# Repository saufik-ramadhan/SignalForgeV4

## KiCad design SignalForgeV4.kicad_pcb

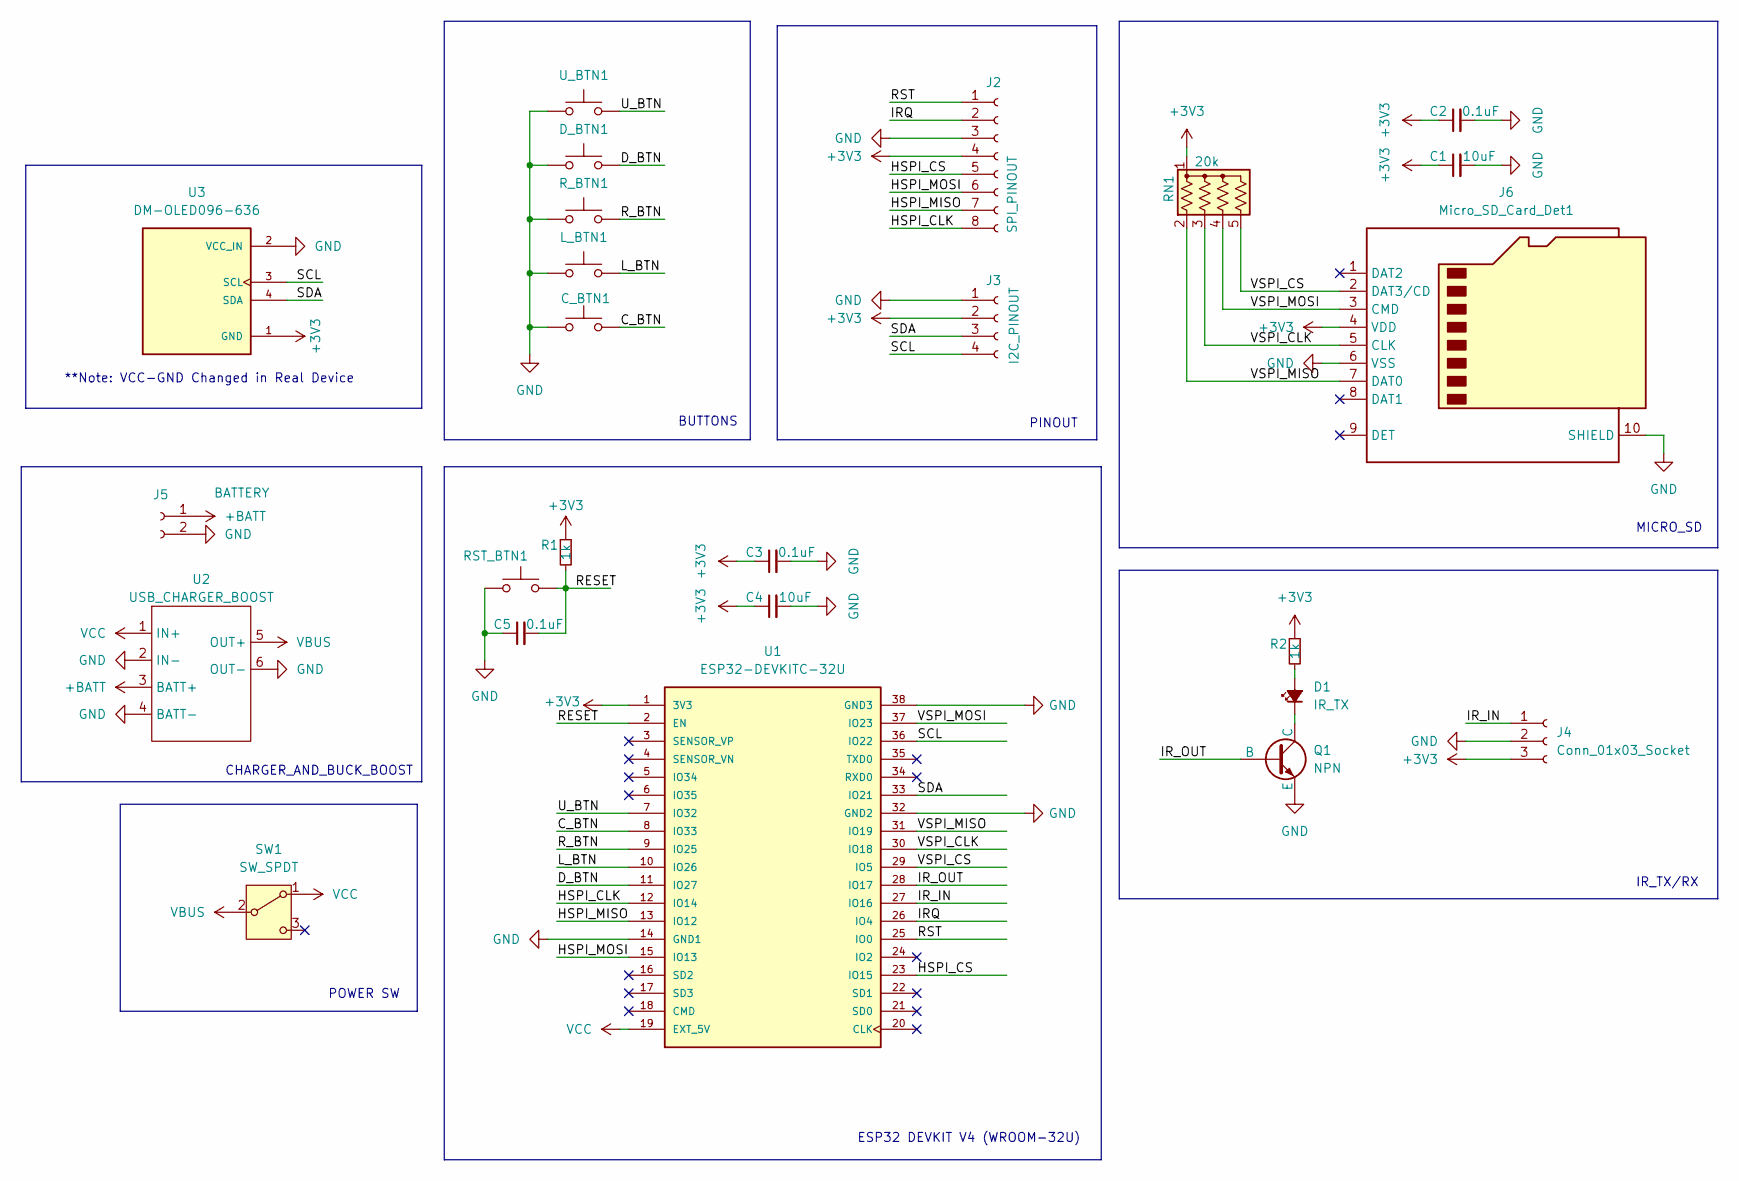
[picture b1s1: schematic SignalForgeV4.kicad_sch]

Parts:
C1, C4: 10uF; C_0805_2012Metric_Pad1.18x1.45mm_HandSolder
C2, C3, C5: 0.1uF; C_0805_2012Metric_Pad1.18x1.45mm_HandSolder
C_BTN1: SW_Push; SW_PUSH_1P1T_6x3.5mm_H5.0_APEM_MJTP1250
D1: IR_TX; PinSocket_1x02_P2.54mm_Vertical
D_BTN1: SW_Push; SW_PUSH_1P1T_6x3.5mm_H5.0_APEM_MJTP1250
J2: SPI_PINOUT; PinSocket_1x08_P2.54mm_Vertical
J3: I2C_PINOUT; PinSocket_1x04_P2.54mm_Vertical
J4: Conn_01x03_Socket; PinSocket_1x03_P2.54mm_Vertical
J5: BATTERY; JST_EH_S2B-EH_1x02_P2.50mm_Horizontal
J6: Micro_SD_Card_Det1; J_SD_Card-micro_socket_A
L_BTN1: SW_Push; SW_PUSH_1P1T_6x3.5mm_H5.0_APEM_MJTP1250
Q1: NPN; SOT-23_Handsoldering
R1, R2: 1k; R_0805_2012Metric_Pad1.20x1.40mm_HandSolder
RN1: 20k; R_Array_Convex_4x0603
RST_BTN1: SW_Push; SW_SPST_FSMSM
R_BTN1: SW_Push; SW_PUSH_1P1T_6x3.5mm_H5.0_APEM_MJTP1250
SW1: SW_SPDT; SW_SPDT_PCM12
U1: ESP32-DEVKITC-32U; MODULE_ESP32-DEVKITC-32U; PARTREV V4
U2: USB_CHARGER_BOOST; USB_Charger_Buck_Boost
U3: DM-OLED096-636; MODULE_DM-OLED096-636; PARTREV 2018-09-10
U_BTN1: SW_Push; SW_PUSH_1P1T_6x3.5mm_H5.0_APEM_MJTP1250

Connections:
+3V3: C1.1, C2.1, C3.1, C4.1, J2.4, J3.2, J4.3, J6.4 (VDD), R1.1, R2.1, RN1.1 (common), U1.1 (3V3), U3.1 (GND)
+BATT: J5.1, U2.3 (BATT+)
/C_BTN: C_BTN1.2, U1.8 (IO33)
/D_BTN: D_BTN1.2, U1.11 (IO27)
/HSPI_CLK: J2.8, U1.12 (IO14)
/HSPI_CS: J2.5, U1.23 (IO15)
/HSPI_MISO: J2.7, U1.13 (IO12)
/HSPI_MOSI: J2.6, U1.15 (IO13)
/IRQ: J2.2, U1.26 (IO4)
/IR_IN: J4.1, U1.27 (IO16)
/IR_OUT: Q1.2 (B), U1.28 (IO17)
/L_BTN: L_BTN1.2, U1.10 (IO26)
/RESET: C5.2, R1.2, RST_BTN1.2, U1.2 (EN)
/RST: J2.1, U1.25 (IO0)
/R_BTN: R_BTN1.2, U1.9 (IO25)
/SCL: J3.4, U1.36 (IO22), U3.3 (SCL)
/SDA: J3.3, U1.33 (IO21), U3.4 (SDA)
/U_BTN: U1.7 (IO32), U_BTN1.2
/VSPI_CLK: J6.5 (CLK), RN1.3 (R2), U1.30 (IO18)
/VSPI_CS: J6.2 (DAT3/CD), RN1.5 (R4), U1.29 (IO5)
/VSPI_MISO: J6.7 (DAT0), RN1.2 (R1), U1.31 (IO19)
/VSPI_MOSI: J6.3 (CMD), RN1.4 (R3), U1.37 (IO23)
GND: C1.2, C2.2, C3.2, C4.2, C5.1, C_BTN1.1, D_BTN1.1, J2.3, J3.1, J4.2, J5.2, J6.6 (VSS), J6.10 (SHIELD), L_BTN1.1, Q1.3 (E), RST_BTN1.1, R_BTN1.1, U1.14 (GND1), U1.32 (GND2), U1.38 (GND3), U2.2 (IN-), U2.4 (BATT-), U2.6 (OUT-), U3.2 (VCC_IN), U_BTN1.1
unnamed: D1.2 (A), R2.2
unnamed: D1.1 (K), Q1.1 (C)
VBUS: SW1.2 (B), U2.5 (OUT+)
VCC: SW1.1 (A), U1.19 (EXT_5V), U2.1 (IN+)

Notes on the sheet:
IR_TX/RX
**Note: VCC-GND Changed in Real Device
MICRO_SD
POWER SW
PINOUT
CHARGER_AND_BUCK_BOOST
BUTTONS
ESP32 DEVKIT V4 (WROOM-32U)

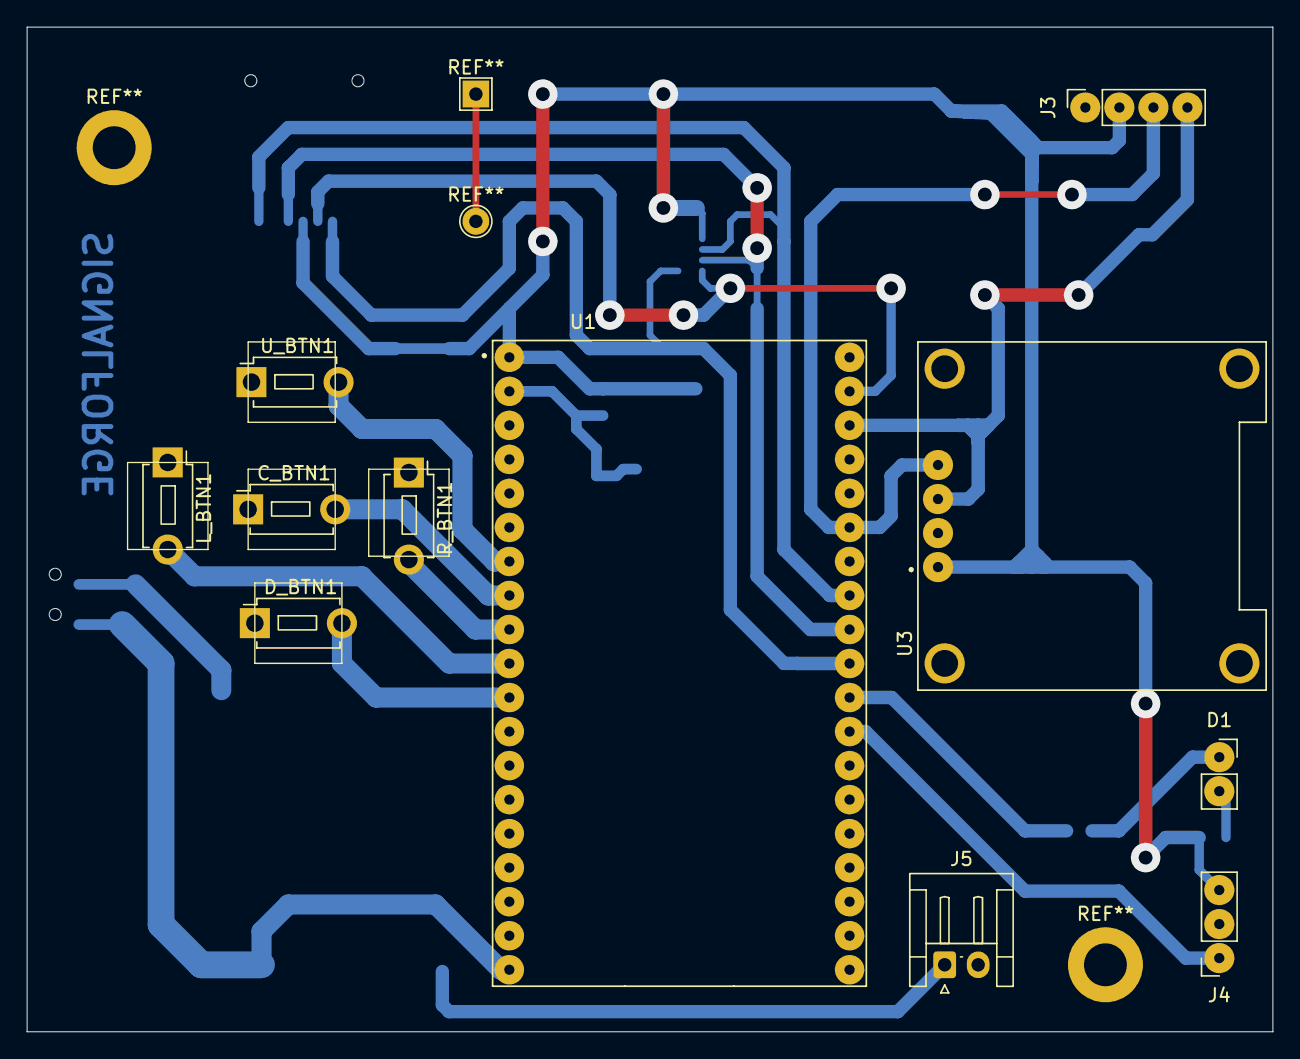
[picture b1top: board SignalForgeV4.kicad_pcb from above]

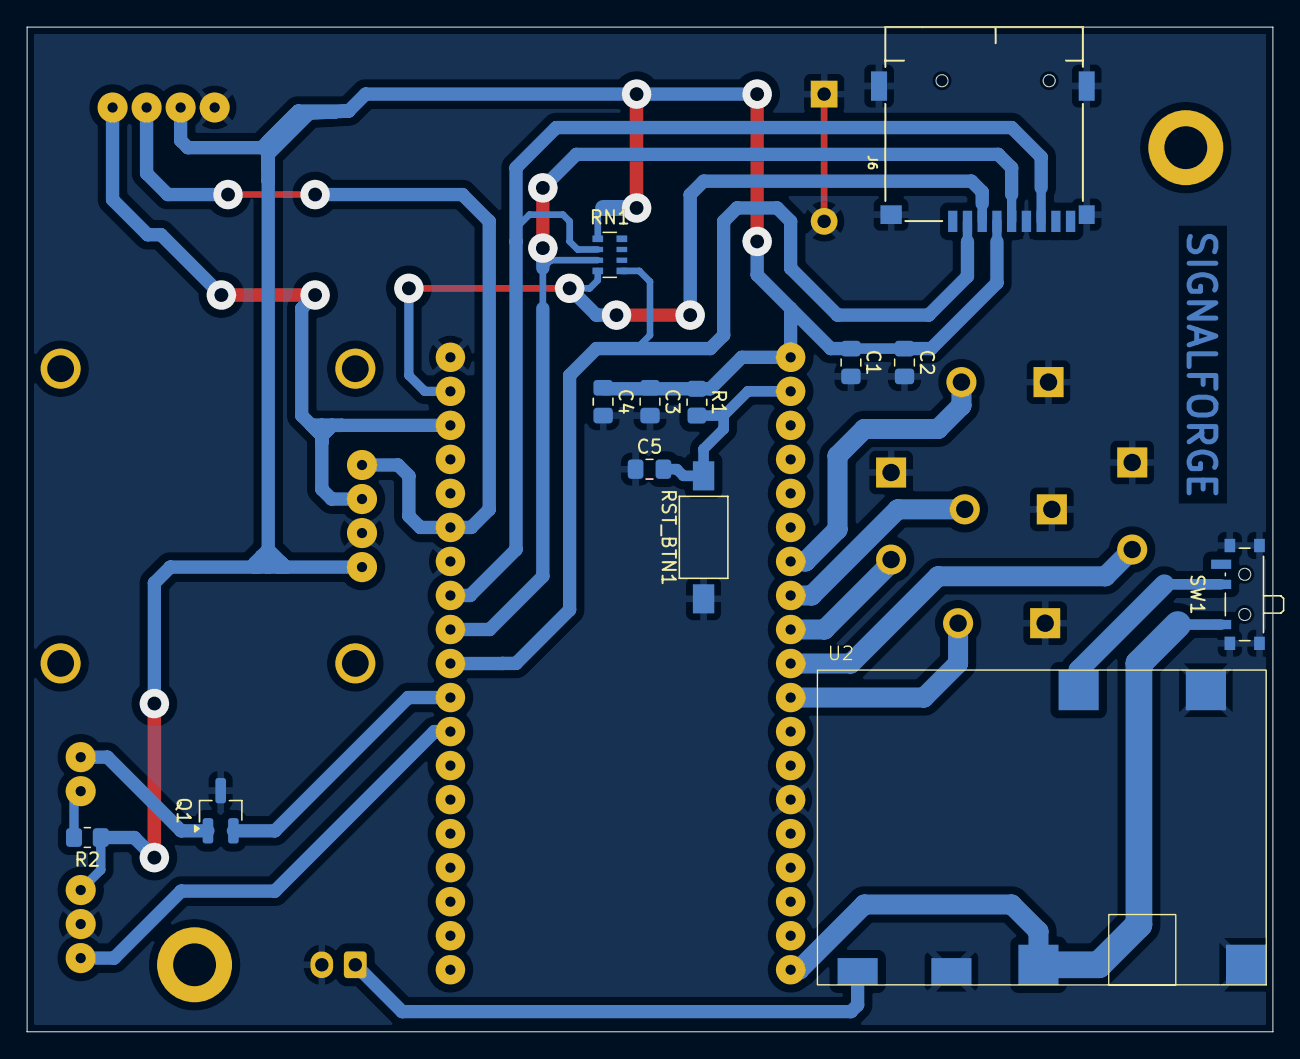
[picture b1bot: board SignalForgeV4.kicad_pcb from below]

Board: 2 copper layers, 93.0 x 75.0 mm, 24 parts (13 on the bottom side), 21 nets.

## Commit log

2024-12-27 feat: signal forge initial commit
2024-12-27 feat: add custom libraries
2024-12-30 fix: update latest jlcpcb
